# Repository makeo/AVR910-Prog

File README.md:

# AVR910 Programmer

This repository contains all files required to build a programmer based on the application note [AVR910](http://ww1.microchip.com/downloads/en/appnotes/atmel-0943-in-system-programming_applicationnote_avr910.pdf) by Atmel.

**WARNING**: This programmer is totally outdated and you should not build it if you need a useable programmer!

You can use this programmer to burn *.ebn* files using *AvrProg*. This is the only valid use case I know of.\
Alternatively, you could search for the illusive *EBN2HEX.exe* to convert the *.ebn* file.

If you're still interested you can start by looking at my board design [here](./pcb).

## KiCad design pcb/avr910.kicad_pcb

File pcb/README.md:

# AVR910 PCB

Notes:
- The ATtiny2313 firmware can be found [here](./../firmware)
- To program the ATtiny2313 you can use the jumper J3 and connect another programmer to the IDC socket
- The MCP2221 be replaced with a PIC16F1454 using [this](https://github.com/jgeisler0303/PIC16F1454_USB2Serial) firmware

BOM:
- 1x ATtiny2313
- 1x MCP2221
- 1x USB 2.0 Female Type-B Jack
- 1x 2.54mm 2x5 Pin IDC Socket
- 1x 10kΩ Resistor
- 3x 0.1uF Ceramic Capacitor
- 1x 7.3728MHz Crystal
- 2x 27pF Ceramic Capacitor
- 1x 3mm Green LED
- 1x 3mm Yellow LED
- 1x 3mm Red LED
- 3x ~3.3kΩ Resistor for LED
- 1x 2.54mm Jumper
- 1x 0.5A Fuse with Holder
- 2.54mm Male Headers

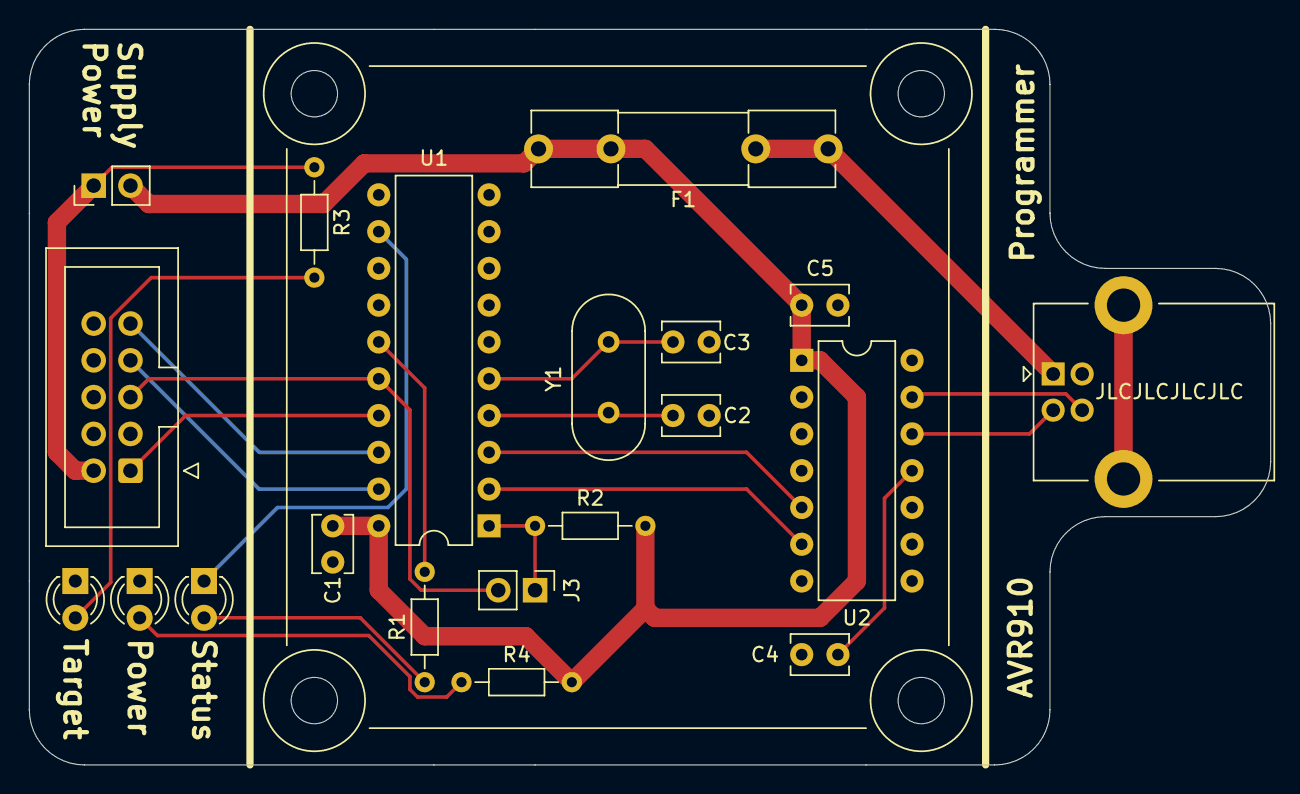
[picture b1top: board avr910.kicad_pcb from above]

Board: 2 copper layers, 85.7 x 50.8 mm, 20 parts (0 on the bottom side), 21 nets.

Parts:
C1, C4, C5: 0.1uF; C_Disc_D3.8mm_W2.6mm_P2.50mm
C2, C3: 27pF; C_Disc_D3.8mm_W2.6mm_P2.50mm
D1, D2, D3: LED; LED_D3.0mm
F1: Fuse; Fuseholder_Clip-5x20mm_Littelfuse_111_Inline_P20.00x5.00mm_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
J1: Conn_02x05_Odd_Even; IDC-Header_2x05_P2.54mm_Vertical
J2, J3: Conn_01x02; PinHeader_1x02_P2.54mm_Vertical
J4: USB_B; USB_B_Lumberg_2411_02_Horizontal
R1, R3, R4: ?Ω; R_Axial_DIN0204_L3.6mm_D1.6mm_P7.62mm_Horizontal
R2: 10kΩ; R_Axial_DIN0204_L3.6mm_D1.6mm_P7.62mm_Horizontal
U1: ATtiny2313A-PU; DIP-20_W7.62mm
U2: MCP2221AxP; DIP-14_W7.62mm
Y1: 7.3728MHz; Crystal_HC49-4H_Vertical

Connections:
+5V: C1.2, C5.1, F1.2, J2.2, R2.2, R4.1, U1.20, U2.1
D+: J4.3, U2.13
D-: J4.2, U2.12
GND: C1.1, C2.2, C3.2, C4.1, C5.2, D1.1, D2.1, J1.4, J1.6, J1.8, J1.10, J4.4, U1.10, U2.14
MISO: J1.9, U1.18
MOSI: J1.1, U1.17
unnamed: C2.1, U1.4, Y1.2
unnamed: C3.1, U1.5, Y1.1
unnamed: C4.2, U2.11
unnamed: D1.2, R3.1
unnamed: D2.2, R4.2
unnamed: D3.1, U1.12
unnamed: D3.2, R1.2
unnamed: F1.1, J4.1
unnamed: J3.1, R2.1, U1.1
unnamed: R1.1, U1.15
RX: U1.2, U2.6
SCK: J1.7, U1.19
TARGET_PWR: J1.2, J2.1, R3.2
TX: U1.3, U2.5
~RESET: J1.5, J3.2, U1.16

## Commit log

2024-01-16 initial release
